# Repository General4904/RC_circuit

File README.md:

# ⚡ PROJECT_NAME – PCB Design (KiCad)

A PCB design created in KiCad as part of my electronics and PCB engineering practice.  
This project includes the schematic, PCB layout, 3D visualization, and simulation results.

---

## 🧩 Overview
- **Tool Used:** KiCad 
- **Microcontroller:**  None  
- **Board Type:** Single-layer 
- **Power:** 12V  
- **Purpose:** Testing concepts, training, portfolio development.

---

## 🛠️ Project Files
- `rc_circuit.kiCad_sch` – Schematic file  
- `rc_circuit.kiCad_pcb` – PCB layout file  
- `Images/` – Screenshots 

---

## 🖼️ Images

### Schematic  

### PCB Layout  

### 3D View  

---

## 🎞️ Simulation  
A short simulation of the circuit:  
`simulation.mp4`

---

## 📌 Author  
**Generalissimo**  
F.F. Tronics Incorporated  
PCB Design Training Series (2025)

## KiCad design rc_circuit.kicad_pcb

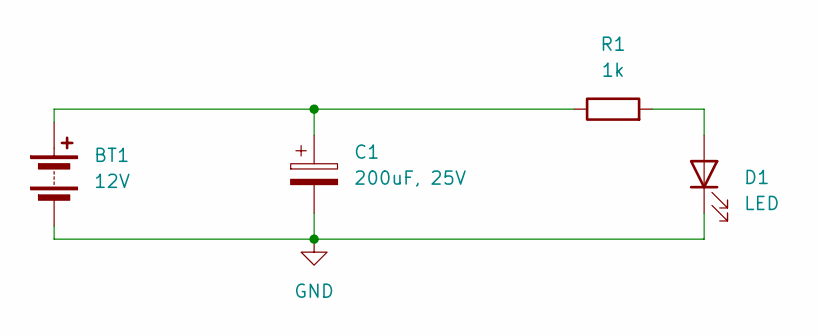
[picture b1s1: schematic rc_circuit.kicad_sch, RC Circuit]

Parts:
BT1: 12V; TerminalBlock_Xinya_XY308-2.54-2P_1x02_P2.54mm_Horizontal
C1: 200uF, 25V; CP_Radial_D4.0mm_P1.50mm
D1: LED; LED_Oval_W5.2mm_H3.8mm
R1: 1k; R_0201_0603Metric

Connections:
GND: BT1.2 (-), C1.2, D1.1 (K)
unnamed: BT1.1 (+), C1.1, R1.1
unnamed: D1.2 (A), R1.2

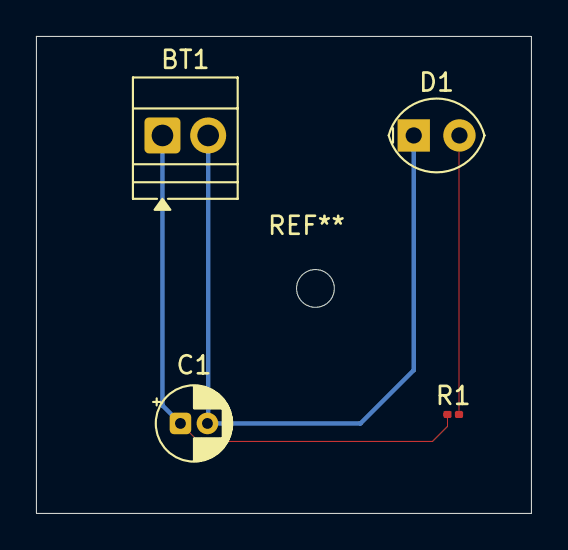
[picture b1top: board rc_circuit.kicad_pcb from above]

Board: 2 copper layers, 27.5 x 26.5 mm, 4 parts (0 on the bottom side), 3 nets.

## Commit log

2025-12-14 Fix simulation file path in README
2025-12-14 Refine project files section in README
    Updated project files section with specific file names and directories.
